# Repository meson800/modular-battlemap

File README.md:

# modular-battlemap

# Goals
We want to make a modular battlemap system that:
- Consists of modular tiles, like 4x4 tiles at 25.4mm scale
- That tiles together with minimal whitespace
- That transmits power/data through the edges
- and is capable of arbitrarly lighting 4 RGB LEDs per square.
- can be powered / controlled from one "base map" tile, that has USB-C output.

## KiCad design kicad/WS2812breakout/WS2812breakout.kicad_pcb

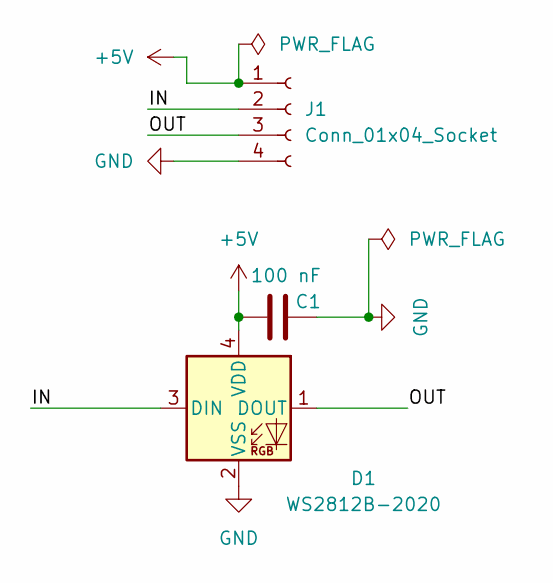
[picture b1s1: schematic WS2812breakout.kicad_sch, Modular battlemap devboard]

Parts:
C1: 100 nF; C_0603_1608Metric
D1: WS2812B-2020; LED_WS2812B-2020_PLCC4_2.0x2.0mm
J1: Conn_01x04_Socket; PinHeader_1x04_P2.54mm_Vertical

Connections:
+5V: C1.1, D1.4 (VDD), J1.1
/IN: D1.3 (DIN), J1.2
/OUT: D1.1 (DOUT), J1.3
GND: C1.2, D1.2 (VSS), J1.4

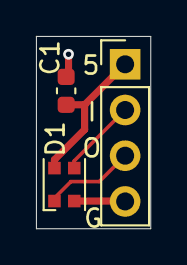
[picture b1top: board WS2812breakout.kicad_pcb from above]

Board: 2 copper layers, 6.4 x 10.7 mm, 3 parts (0 on the bottom side), 4 nets.

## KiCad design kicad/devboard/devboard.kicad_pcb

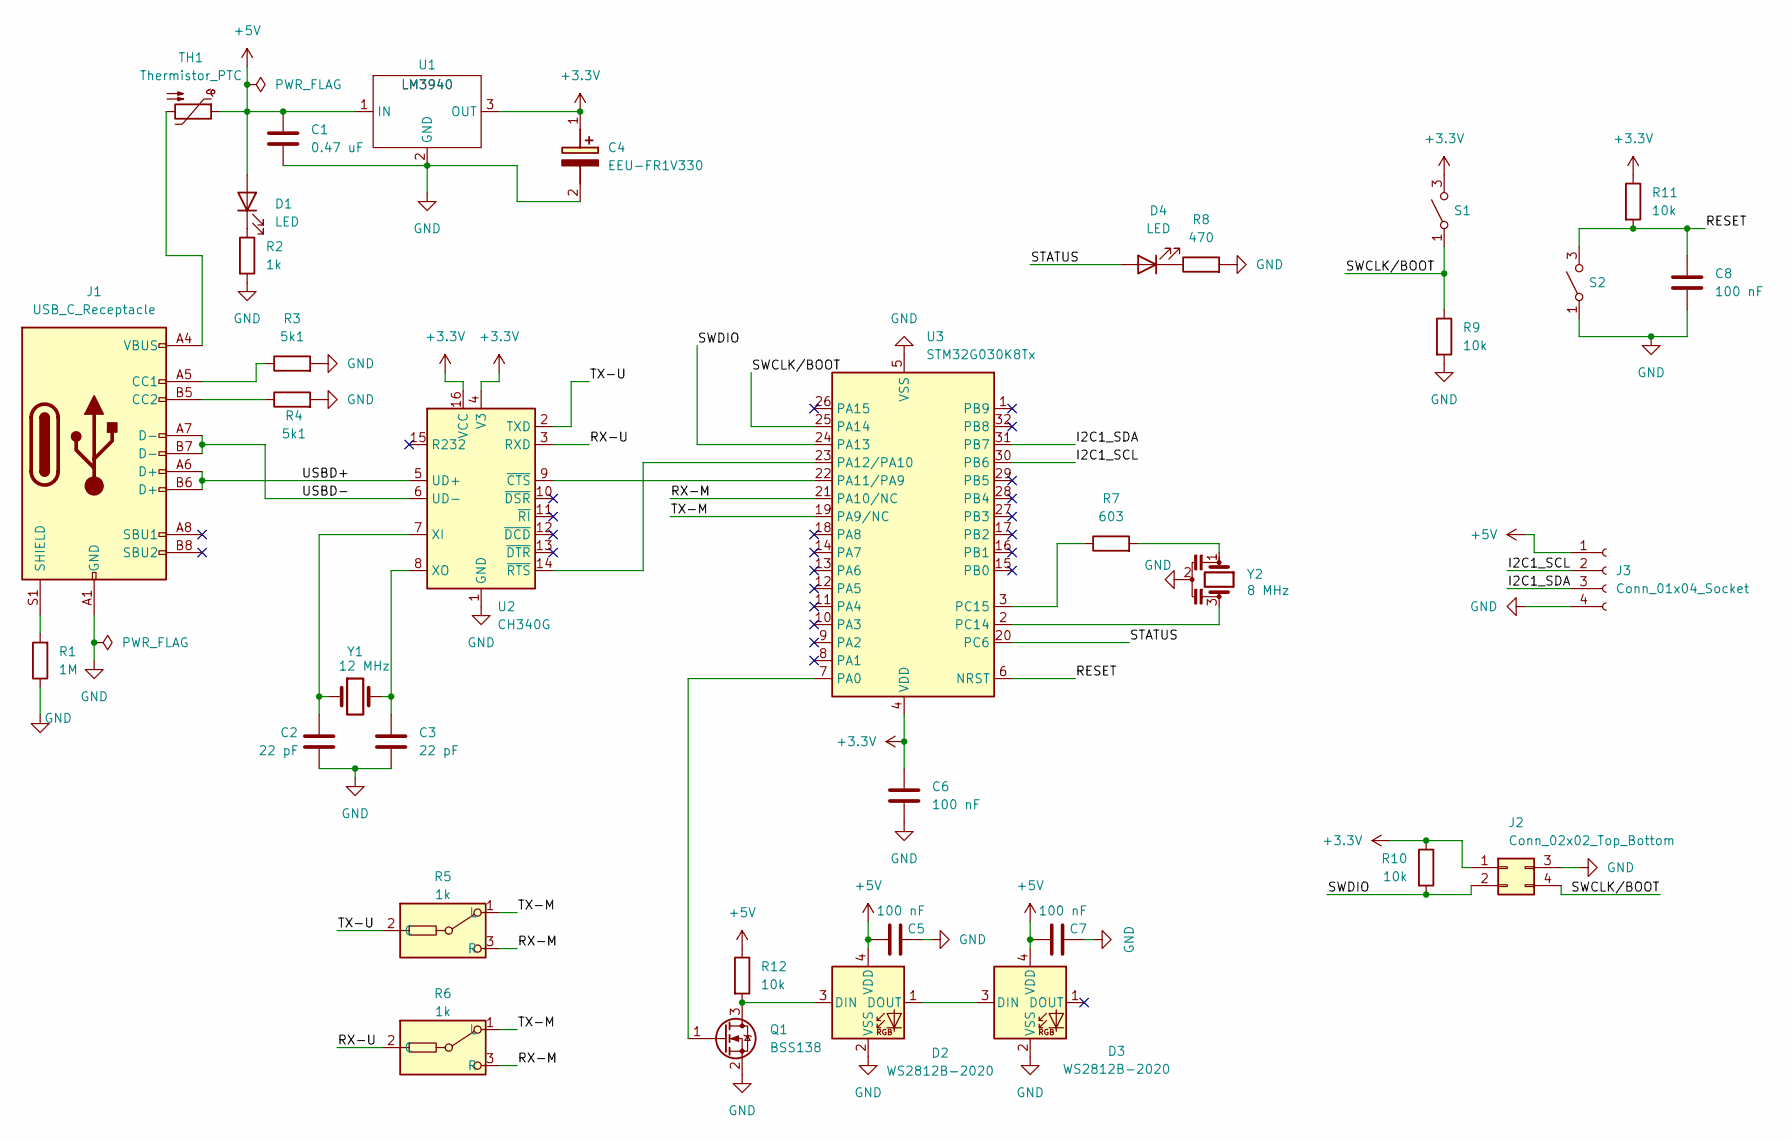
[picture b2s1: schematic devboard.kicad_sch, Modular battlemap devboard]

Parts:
C1: 0.47 uF; C_0603_1608Metric
C2, C3: 22 pF; C_0603_1608Metric
C4: EEU-FR1V330; EEU-FR1330; Mouser Part Number 667-EEU-FR1V330
C5, C6, C7, C8: 100 nF; C_0603_1608Metric
D1, D4: LED; LED_0603_1608Metric
D2, D3: WS2812B-2020; LED_WS2812B-2020_PLCC4_2.0x2.0mm
J1: USB_C_Receptacle; USB_C_Receptacle_Palconn_UTC16-G_pcb_edge
J2: Conn_02x02_Top_Bottom; PinHeader_2x02_P2.54mm_Vertical
J3: Conn_01x04_Socket; PinHeader_1x04_P2.54mm_Vertical
Q1: BSS138; SOT-23
R1: 1M; R_0603_1608Metric
R2: 1k; R_0603_1608Metric
R3, R4: 5k1; R_0603_1608Metric
R5, R6: 1k; resistor_3pad_switch_0603
R7: 603; R_0603_1608Metric
R8: 470; R_0603_1608Metric
R9, R10, R11, R12: 10k; R_0603_1608Metric
S1, S2: PTS526SM15SMTR2LFS; Mouser Part Number 611-PTS526SM15SMTR2L
TH1: Thermistor_PTC; Eaton PTS120616V025
U1: LM3940
U2: CH340G; SOIC-16_3.9x9.9mm_P1.27mm
U3: STM32G030K8Tx; LQFP-32_7x7mm_P0.8mm
Y1: 12 MHz; Crystal_HC49-4H_Vertical
Y2: 8 MHz; CSTNE16M0V530000R0; Mouser Part Number 81-CSTNE8M00G550000R

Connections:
+3.3V: C4.1 (+), C6.1, J2.1, R10.1, R11.1, S1.3, S1.4, U1.3 (OUT), U2.4 (V3), U2.16 (VCC), U3.4 (VDD)
+5V: C1.1, C5.1, C7.1, D1.2 (A), D2.4 (VDD), D3.4 (VDD), J3.1, R12.1, TH1.1, U1.1 (IN)
/I2C1_SCL: J3.2, U3.30 (PB6)
/I2C1_SDA: J3.3, U3.31 (PB7)
/RESET: C8.1, R11.2, S2.3, S2.4, U3.6 (NRST)
/RX-M: R5.3 (R), R6.3 (R), U3.21 (PA10/NC)
/RX-U: R6.2 (C), U2.3 (RXD)
/STATUS: D4.2 (A), U3.20 (PC6)
/SWCLK/BOOT: J2.4, R9.1, S1.1, S1.2, U3.25 (PA14)
/SWDIO: J2.2, R10.2, U3.24 (PA13)
/TX-M: R5.1 (L), R6.1 (L), U3.19 (PA9/NC)
/TX-U: R5.2 (C), U2.2 (TXD)
/USBD+: J1.A6 (D+), J1.B6 (D+), U2.5 (UD+)
/USBD-: J1.A7 (D-), J1.B7 (D-), U2.6 (UD-)
GND: C1.2, C2.2, C3.2, C4.2 (-), C5.2, C6.2, C7.2, C8.2, D2.2 (VSS), D3.2 (VSS), J1.A1 (GND), J1.A12 (GND), J1.B1 (GND), J1.B12 (GND), J2.3, J3.4, Q1.2 (S), R1.1, R2.2, R3.2, R4.2, R8.2, R9.2, S2.1, S2.2, U1.2 (GND), U1.4, U2.1 (GND), U3.5 (VSS), Y2.2
unnamed: D1.1 (K), R2.1
unnamed: D2.3 (DIN), Q1.3 (D), R12.2
unnamed: D2.1 (DOUT), D3.3 (DIN)
unnamed: D4.1 (K), R8.1
unnamed: J1.A5 (CC1), R3.1
unnamed: J1.B5 (CC2), R4.1
unnamed: J1.S1 (SHIELD), R1.2
unnamed: J1.A4 (VBUS), J1.A9 (VBUS), J1.B4 (VBUS), J1.B9 (VBUS), TH1.2
unnamed: Q1.1 (G), U3.7 (PA0)
unnamed: R7.2, Y2.1
unnamed: C2.1, U2.7 (XI), Y1.1
unnamed: C3.1, U2.8 (XO), Y1.2
unnamed: U2.9 (~CTS), U3.22 (PA11/PA9)
unnamed: U2.14 (~RTS), U3.23 (PA12/PA10)
unnamed: U3.2 (PC14), Y2.3
unnamed: R7.1, U3.3 (PC15)

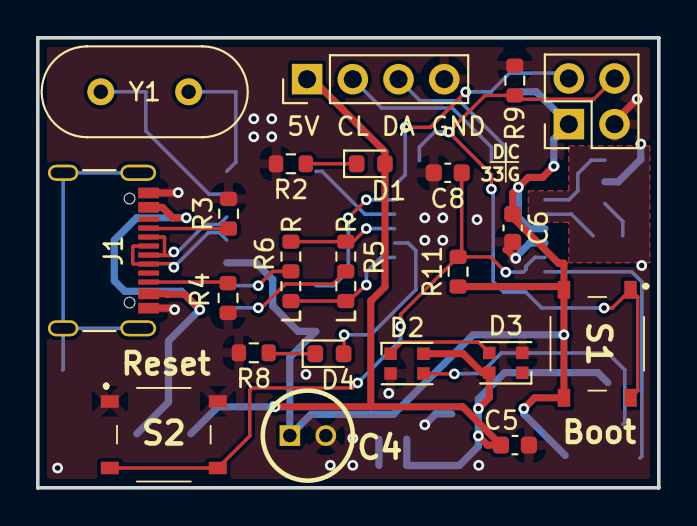
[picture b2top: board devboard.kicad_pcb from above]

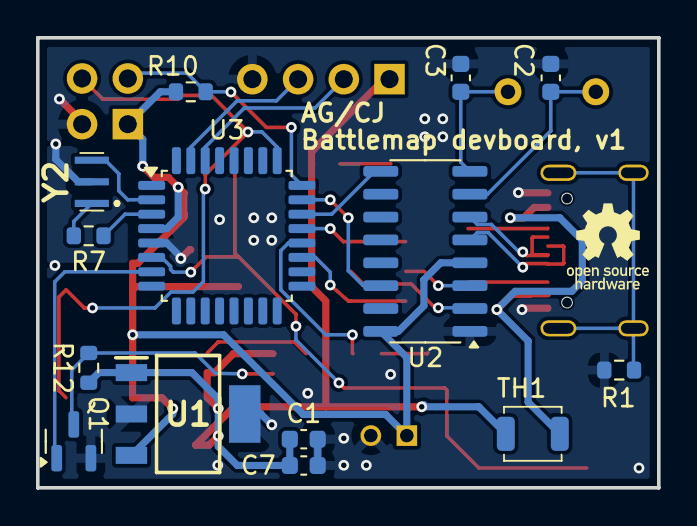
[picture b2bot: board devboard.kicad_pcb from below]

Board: 2 copper layers, 34.5 x 25.0 mm, 36 parts (14 on the bottom side), 31 nets.

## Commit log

2024-05-25 Basic project intro
2024-05-26 Added references
2024-05-27 Initial kicad commit
2024-05-27 Version 1 of the schematic
2024-05-27 Added aliexpress order info, removed modular battlemap
2024-05-27 Simplified project layout, added aliexpress order info
2024-05-28 Reorganized project
2024-05-29 added many many footprints
2024-05-29 all but thermistor footprint added
2024-05-30 Updated footprint assignments and schematic
2024-05-30 Added pin headers for SWD
2024-05-30 Updated boot/swclk net name
2024-05-30 updated footprints for Y1, C2
2024-05-30 All footprints done?
2024-05-30 fixed footprint for crystal
2024-05-30 Added new 16-pin USB C symbol, updated PCB
2024-05-31 Try placing more components on the board
2024-05-31 Move connectors to the top
2024-05-31 Add USB C routing references
2024-05-31 Added 3pad resistor comment, and spread the board out
2024-05-31 Placed components within shape
    it's messy but it fits
2024-05-31 started wiring
2024-06-01 Added MOSFET to drive LEDs
2024-06-02 integrated and added transistor to pcb
2024-06-02 reconfigured slightly
2024-06-02 mostly routed
2024-06-02 ROUTED!!!!
2024-06-02 closed everything
2024-06-02 Updated fresh layout of pieces
2024-06-02 created WS2812 breakout board
2024-06-02 Added most routing, besides the debug header
2024-06-02 routed remaining components
2024-06-02 updated breakout schematic to include in/out lines
2024-06-02 Fixed USB routing, simplified other routes
2024-06-02 Routed and Prettied-up breakout board
2024-06-02 Added ground plane, fully routed
2024-06-02 Finalized, fixing all ERC and DRC warnings
2024-06-02 Move the C4 label
2024-06-02 niche GND prettying up
2024-06-03 Added silkscreen labels
2024-06-03 Updated silkscreen for breakout
2024-06-03 final fixes
